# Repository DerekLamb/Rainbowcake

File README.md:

# Rainbowcake
RGB split keyboard based on Lily58/Sofle and Corne keyboards  
*Currently on first revision*
*Making changes to qmk layout*  

Couldn't find the keyboard for me, so I made it.  

Based on Sofle/Lily58, with Corne style key backlighting  

Designed to use screws and locknuts to tent. 

* ~~PCB ordered on 12/17 from JLCPCB.com~~
* ~~Partially Assembled~~
* ~~Flashed QMK~~
* Need to make changes to layout

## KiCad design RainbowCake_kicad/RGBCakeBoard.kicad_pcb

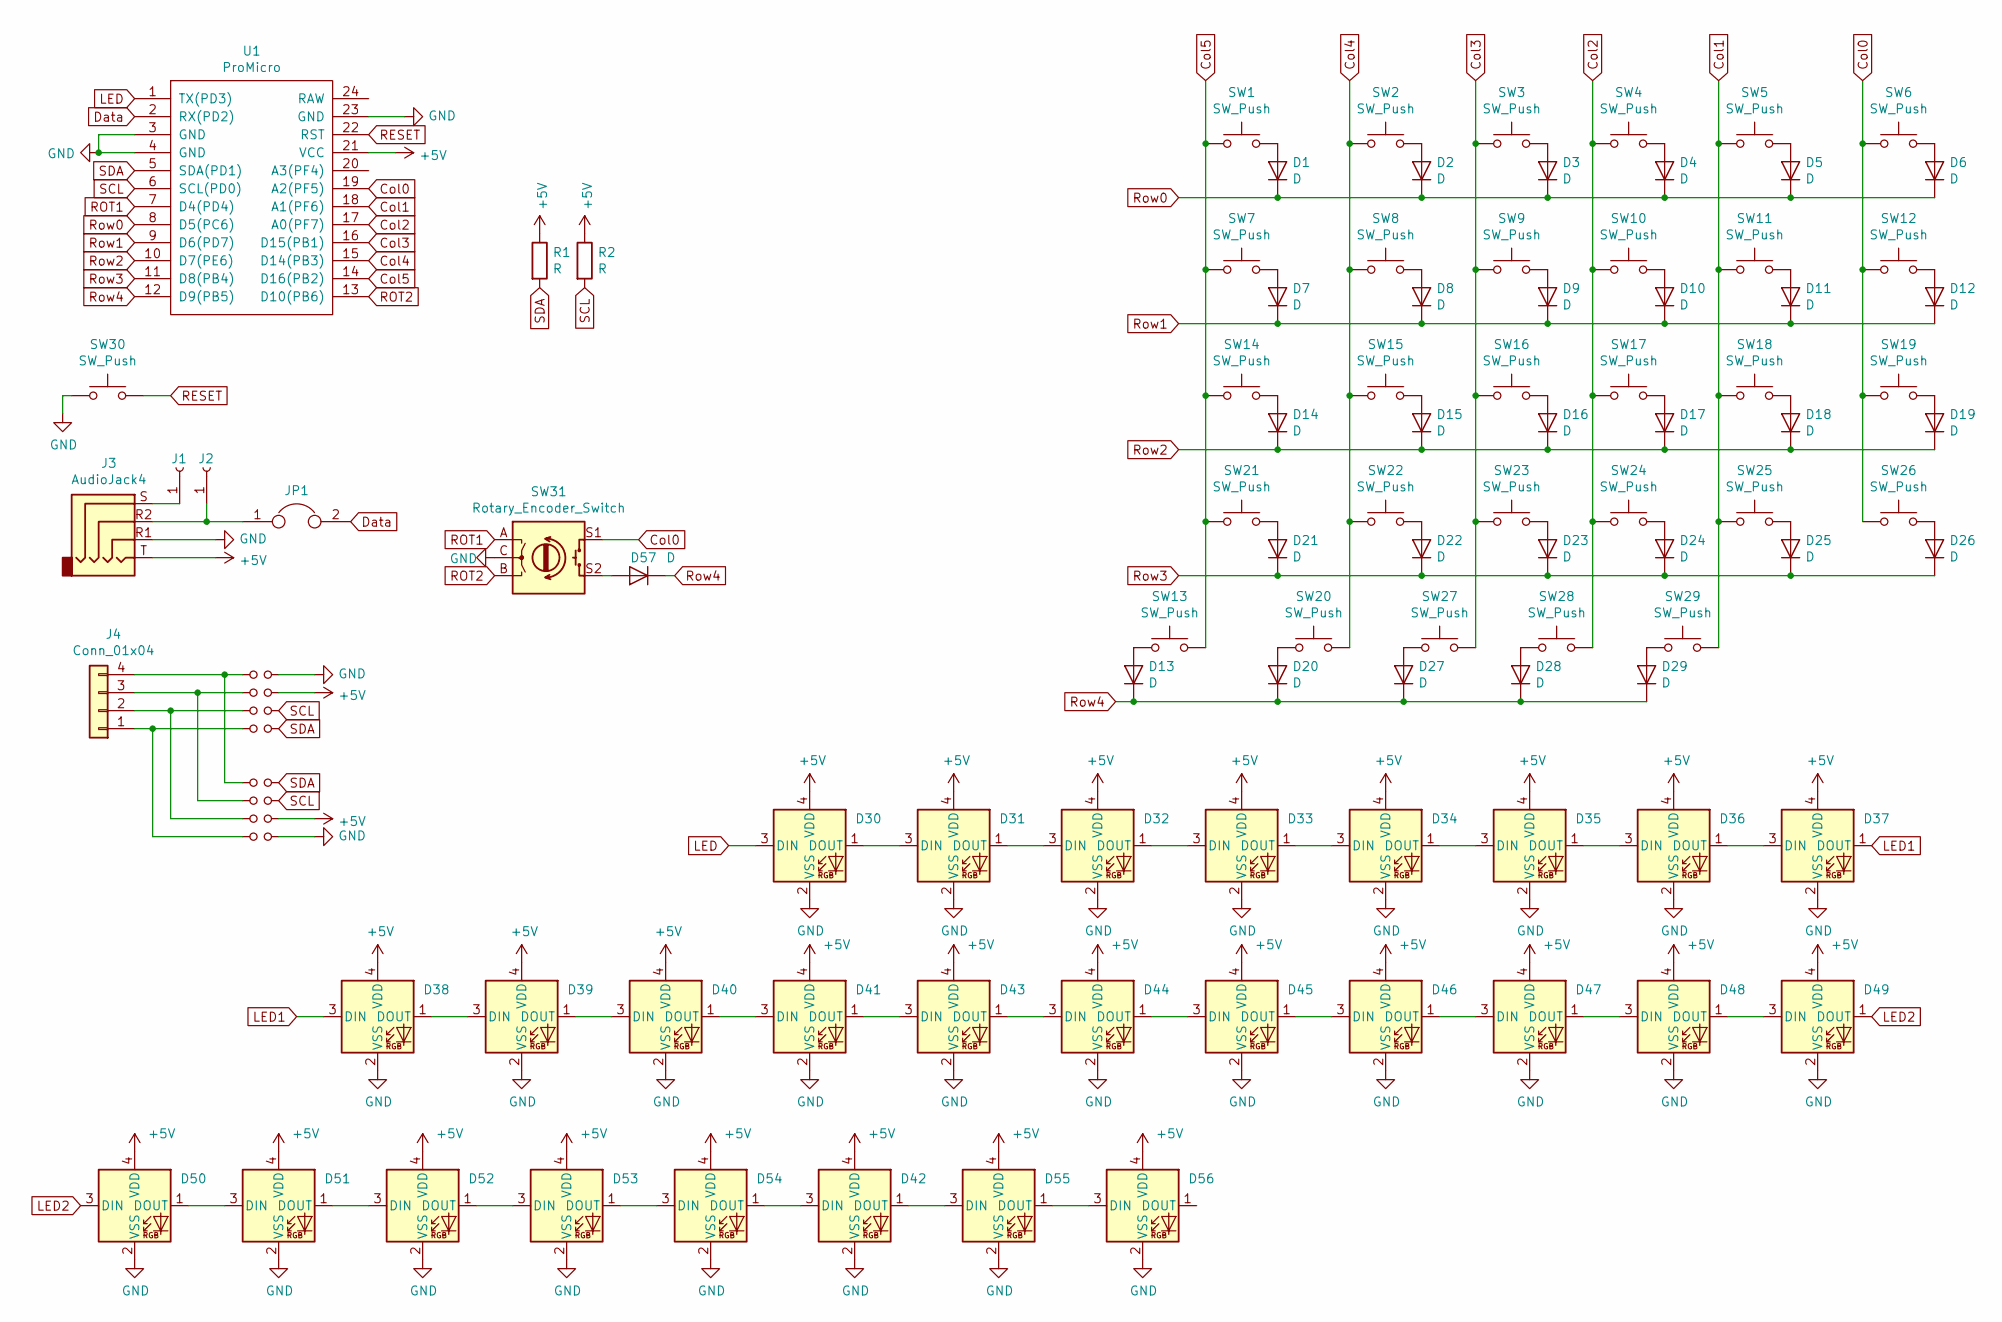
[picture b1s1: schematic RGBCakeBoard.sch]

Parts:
D1, D2, D3, D4, D5, D6, D7, D8, D9, D10, D11, D12, D13, D14, D15, D16, D17, D18, D19, D20, D21, D22, D23, D24, D25, D26, D27, D28, D29, D57: D; Diode_SOD123_Doublesided_Universal
D30, D31, D32, D33, D34, D35, D36, D37, D38, D39, D40, D41, D42, D43, D44, D45, D46, D47, D48, D49, D50, D51, D52, D53, D54, D55, D56: SK6812MINI; SK6812MINI_Cutout
J1, J2: Conn_01x01_Female; SolderWirePad_1x01_Drill1mm
J3: AudioJack4; MJ-4PP-9
J4: Conn_01x04; PinHeader_1x04_P2.54mm_Vertical
JP1: Jumper; SolderJumper-2_P1.3mm_Bridged_RoundedPad1.0x1.5mm
JP2, JP3, JP4, JP5, JP6, JP7, JP8, JP9: Jumper_NO_Small; SolderJumper-2_P1.3mm_Open_RoundedPad1.0x1.5mm
R1, R2: R; R_Axial_DIN0207_L6.3mm_D2.5mm_P10.16mm_Horizontal
SW1, SW2, SW3, SW4, SW5, SW6, SW7, SW8, SW9, SW10, SW11, SW12, SW13, SW14, SW15, SW16, SW17, SW18, SW19, SW20, SW21, SW22, SW23, SW24, SW25, SW26, SW27, SW28, SW29: SW_Push; CherryMX_KailhLowProfile_Hotswap_edge
SW30: SW_Push; SW_Push_1P1T_NO_CK_KMR2
SW31: Rotary_Encoder_Switch; XDCR_PEC11R-4215F
U1: ProMicro; ProMicro_rev2

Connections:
+5V: D30.4 (VDD), D31.4 (VDD), D32.4 (VDD), D33.4 (VDD), D34.4 (VDD), D35.4 (VDD), D36.4 (VDD), D37.4 (VDD), D38.4 (VDD), D39.4 (VDD), D40.4 (VDD), D41.4 (VDD), D42.4 (VDD), D43.4 (VDD), D44.4 (VDD), D45.4 (VDD), D46.4 (VDD), D47.4 (VDD), D48.4 (VDD), D49.4 (VDD), D50.4 (VDD), D51.4 (VDD), D52.4 (VDD), D53.4 (VDD), D54.4 (VDD), D55.4 (VDD), D56.4 (VDD), J3.T, JP3.2, JP8.2, R1.1, R2.1, U1.21 (VCC); also elsewhere on the board
Col0: SW6.1, SW12.1, SW19.1, SW26.1, SW31.S1, U1.19 (A2(PF5))
Col1: SW5.1, SW11.1, SW18.1, SW25.1, SW29.2, U1.18 (A1(PF6))
Col2: SW4.1, SW10.1, SW17.1, SW24.1, SW28.2, U1.17 (A0(PF7))
Col3: SW3.1, SW9.1, SW16.1, SW23.1, SW27.2, U1.16 (D15(PB1))
Col4: SW2.1, SW8.1, SW15.1, SW20.2, SW22.1, U1.15 (D14(PB3))
Col5: SW1.1, SW7.1, SW13.2, SW14.1, SW21.1, U1.14 (D16(PB2))
Data: JP1.2, U1.2 (RX(PD2))
GND: D30.2 (VSS), D31.2 (VSS), D32.2 (VSS), D33.2 (VSS), D34.2 (VSS), D35.2 (VSS), D36.2 (VSS), D37.2 (VSS), D38.2 (VSS), D39.2 (VSS), D40.2 (VSS), D41.2 (VSS), D42.2 (VSS), D43.2 (VSS), D44.2 (VSS), D45.2 (VSS), D46.2 (VSS), D47.2 (VSS), D48.2 (VSS), D49.2 (VSS), D50.2 (VSS), D51.2 (VSS), D52.2 (VSS), D53.2 (VSS), D54.2 (VSS), D55.2 (VSS), D56.2 (VSS), J3.R1, JP2.2, JP9.2, SW30.1, SW31.C, U1.3 (GND), U1.4 (GND), U1.23 (GND); also elsewhere on the board
LED: D30.3 (DIN), U1.1 (TX(PD3))
LED1: D37.1 (DOUT), D38.3 (DIN)
LED2: D49.1 (DOUT), D50.3 (DIN)
unnamed: D1.2 (A), SW1.2
unnamed: D2.2 (A), SW2.2
unnamed: D3.2 (A), SW3.2
unnamed: D4.2 (A), SW4.2
unnamed: D5.2 (A), SW5.2
unnamed: D6.2 (A), SW6.2
unnamed: D7.2 (A), SW7.2
unnamed: D8.2 (A), SW8.2
unnamed: D9.2 (A), SW9.2
unnamed: D10.2 (A), SW10.2
unnamed: D11.2 (A), SW11.2
unnamed: D12.2 (A), SW12.2
unnamed: D13.2 (A), SW13.1
unnamed: D14.2 (A), SW14.2
unnamed: D15.2 (A), SW15.2
unnamed: D16.2 (A), SW16.2
unnamed: D17.2 (A), SW17.2
unnamed: D18.2 (A), SW18.2
unnamed: D19.2 (A), SW19.2
unnamed: D20.2 (A), SW20.1
unnamed: D21.2 (A), SW21.2
unnamed: D22.2 (A), SW22.2
unnamed: D23.2 (A), SW23.2
unnamed: D24.2 (A), SW24.2
unnamed: D25.2 (A), SW25.2
unnamed: D26.2 (A), SW26.2
unnamed: D27.2 (A), SW27.1
unnamed: D28.2 (A), SW28.1
unnamed: D29.2 (A), SW29.1
unnamed: D30.1 (DOUT), D31.3 (DIN)
unnamed: D31.1 (DOUT), D32.3 (DIN)
unnamed: D32.1 (DOUT), D33.3 (DIN)
unnamed: D33.1 (DOUT), D34.3 (DIN)
unnamed: D34.1 (DOUT), D35.3 (DIN)
unnamed: D35.1 (DOUT), D36.3 (DIN)
unnamed: D36.1 (DOUT), D37.3 (DIN)
unnamed: D38.1 (DOUT), D39.3 (DIN)
unnamed: D39.1 (DOUT), D40.3 (DIN)
unnamed: D40.1 (DOUT), D41.3 (DIN)
unnamed: D41.1 (DOUT), D43.3 (DIN)
unnamed: D42.1 (DOUT), D55.3 (DIN)
unnamed: D42.3 (DIN), D54.1 (DOUT)
unnamed: D43.1 (DOUT), D44.3 (DIN)
unnamed: D44.1 (DOUT), D45.3 (DIN)
unnamed: D45.1 (DOUT), D46.3 (DIN)
unnamed: D46.1 (DOUT), D47.3 (DIN)
unnamed: D47.1 (DOUT), D48.3 (DIN)
unnamed: D48.1 (DOUT), D49.3 (DIN)
unnamed: D50.1 (DOUT), D51.3 (DIN)
unnamed: D51.1 (DOUT), D52.3 (DIN)
unnamed: D52.1 (DOUT), D53.3 (DIN)
unnamed: D53.1 (DOUT), D54.3 (DIN)
unnamed: D55.1 (DOUT), D56.3 (DIN)
unnamed 65: D56.1 (DOUT); also elsewhere on the board
unnamed: D57.2 (A), SW31.S2
unnamed: J1.1, J3.S
unnamed: J2.1, J3.R2, JP1.1
unnamed: J4.1, JP5.1, JP9.1
unnamed: J4.2, JP4.1, JP8.1
unnamed: J4.3, JP3.1, JP7.1
unnamed: J4.4, JP2.1, JP6.1
RESET: SW30.2, U1.22 (RST)
ROT1: SW31.A, U1.7 (D4(PD4))
ROT2: SW31.B, U1.13 (D10(PB6))
Row0: D1.1 (K), D2.1 (K), D3.1 (K), D4.1 (K), D5.1 (K), D6.1 (K), U1.8 (D5(PC6))
Row1: D7.1 (K), D8.1 (K), D9.1 (K), D10.1 (K), D11.1 (K), D12.1 (K), U1.9 (D6(PD7))
Row2: D14.1 (K), D15.1 (K), D16.1 (K), D17.1 (K), D18.1 (K), D19.1 (K), U1.10 (D7(PE6))
Row3: D21.1 (K), D22.1 (K), D23.1 (K), D24.1 (K), D25.1 (K), D26.1 (K), U1.11 (D8(PB4))
Row4: D13.1 (K), D20.1 (K), D27.1 (K), D28.1 (K), D29.1 (K), D57.1 (K), U1.12 (D9(PB5))
SCL: JP4.2, JP7.2, R2.2, U1.6 (SCL(PD0))
SDA: JP5.2, JP6.2, R1.2, U1.5 (SDA(PD1))

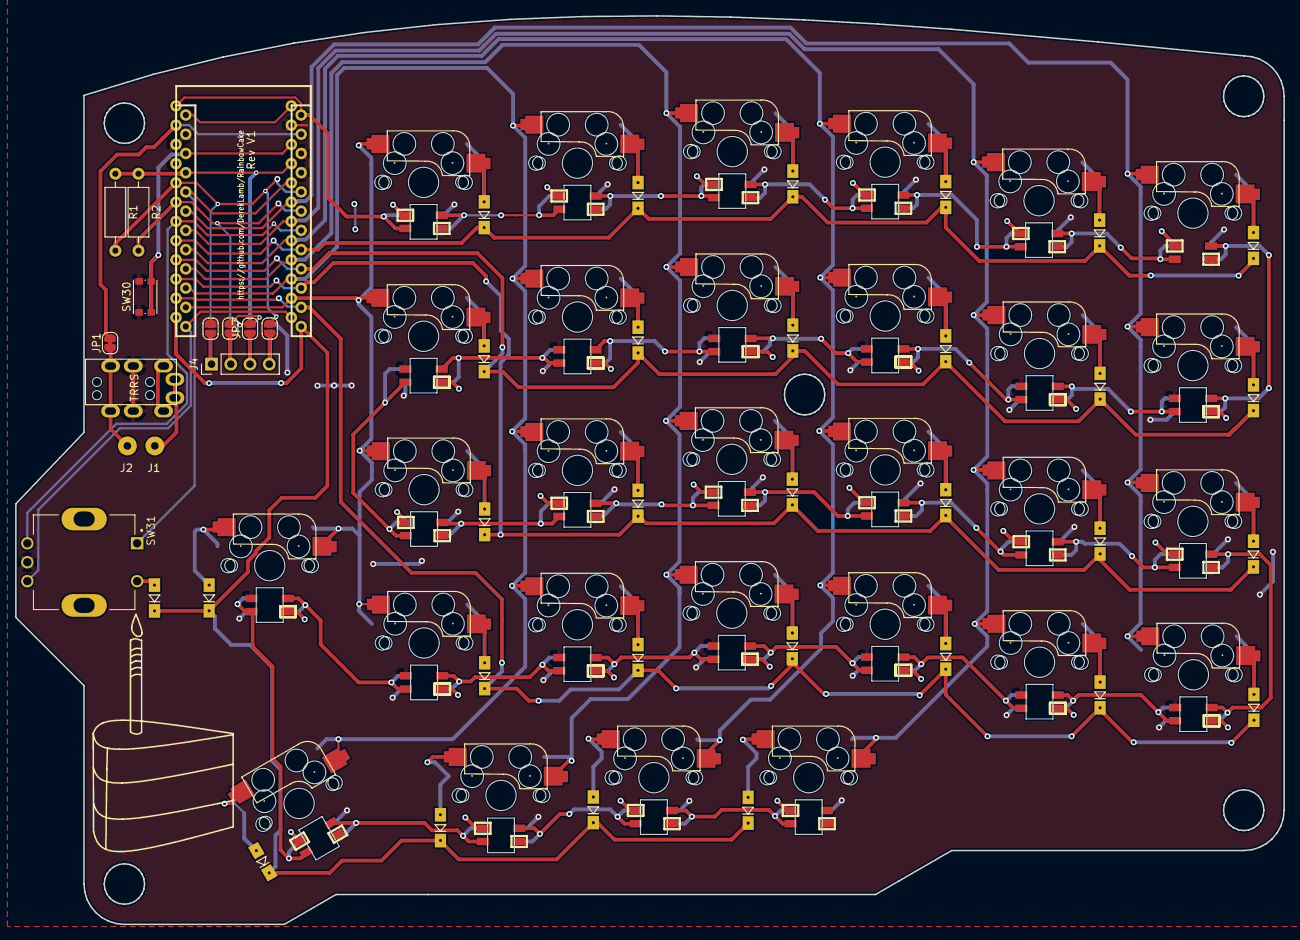
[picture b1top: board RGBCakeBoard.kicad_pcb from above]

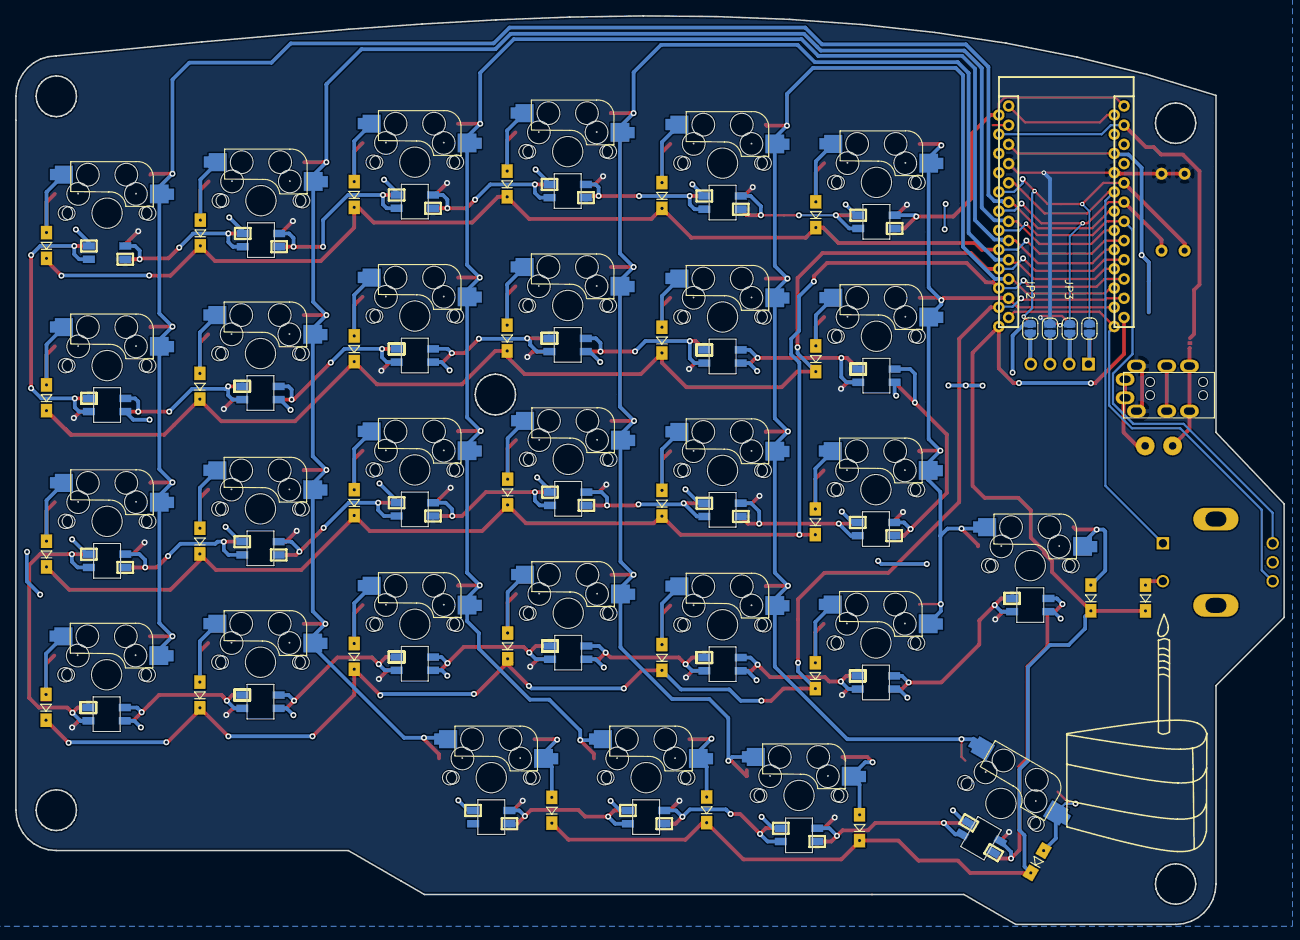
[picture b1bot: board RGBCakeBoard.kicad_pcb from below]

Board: 2 copper layers, 167.5 x 120.0 mm, 106 parts (4 on the bottom side), 84 nets.

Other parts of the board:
D57#2, D58: SK6812MINI; SK6812MINI_Cutout

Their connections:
+5V: D57#2.4, D58.4; also elsewhere on the board
GND: D57#2.2, D58.2; also elsewhere on the board
unnamed 65: D57#2.3; also elsewhere on the board
unnamed: D57#2.1, D58.3
